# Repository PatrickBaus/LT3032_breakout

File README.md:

LT3032
===================

This repository contains the KiCAD PCB project files for a breakout board for the Linear Technologies LT3032 dual 150 mA,
positive/negative, low noise, LDO (http://www.linear.com/product/LT3032).

About
-----
This breakout board only supports the fixed voltage versions of the LT3032. There are 4 version available:
 * ±3.3V
 * ±5V
 * ±12V
 * ±15V

The root folder contains the KiCAD files and the bill of materials, while the gerber files can be found in the [/gerber](gerber/) folder.

Related Repositories
-------------

See the following repositories for more information

KiCAD footprints: https://github.com/PatrickBaus/footprints.pretty

KiCAD 3D models: https://github.com/PatrickBaus/footprints.3dshapes

KiCAD schematic libraries: https://github.com/PatrickBaus/KiCad-libraries

License
-------

This work is released under the Cern OHL v.1.2
See www.ohwr.org/licenses/cern-ohl/v1.2 or the included LICENSE file for more information.

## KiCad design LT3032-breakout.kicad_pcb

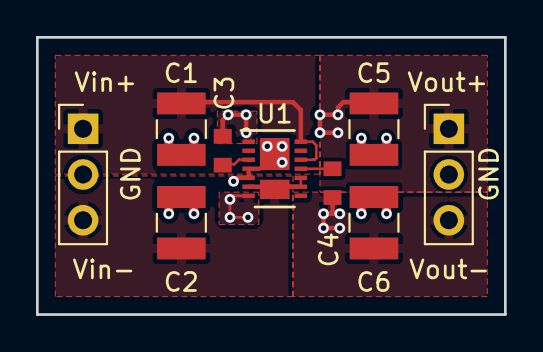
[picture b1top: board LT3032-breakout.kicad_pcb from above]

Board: 2 copper layers, 26.0 x 15.4 mm, 9 parts (0 on the bottom side), 7 nets.

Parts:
C1, C2, C5, C6: 10u; C_1210_3225Metric
C3, C4: 10n; C_0603_1608Metric
J1: Input; PinHeader_1x03_P2.54mm_Vertical
J2: Output; PinHeader_1x03_P2.54mm_Vertical
U1: LT3032-X; Linear_DE14MA

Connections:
/INN: C2.1, J1.3, U1.6, U1.9, U1.10, U1.16
/INP: C1.2, J1.1, U1.12, U1.14
GND: C1.1, C2.2, C5.1, C6.2, J1.2, J2.2, U1.4, U1.5, U1.15
unnamed: C3.1, U1.3
unnamed: C3.2, C5.2, J2.1, U1.1
unnamed: C4.1, C6.1, J2.3, U1.7
unnamed: C4.2, U1.11

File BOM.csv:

"Date:","2018-05-22T07:05:02 CEST"
"Tool:","Eeschema (5.0-dev-4069-g322ce84fb)"
"Component Count:","9"
"Ref","Qnty","Value","Cmp name","Footprint","Description","Vendor"
"C1, C2, C5, C6, ","4","10u","GMK325BJ106KN-T","Capacitor_SMD:C_1210_3225Metric","Unpolarized capacitor","Taiyo Yuden"
"C3, C4, ","2","10n","GRM1885C1H103JA01J","Capacitor_SMD:C_0603_1608Metric","Unpolarized capacitor","Murata"
"J1, ","1","Input","4-103741-0","Connector_PinHeader_2.54mm:PinHeader_1x03_P2.54mm_Vertical","Generic connector, single row, 01x03, script generated (kicad-library-utils/schlib/autogen/connector/)","TE Connectivity"
"J2, ","1","Output","4-103741-0","Connector_PinHeader_2.54mm:PinHeader_1x03_P2.54mm_Vertical","Generic connector, single row, 01x03, script generated (kicad-library-utils/schlib/autogen/connector/)","TE Connectivity"
"U1, ","1","LT3032-X","LT3032-X","Package_DFN_QFN:Linear_DE14MA","Dual 150mA, Positive/Negative Low Noise, Low Dropout Linear Regulator, Fixed Output","Linear Technology"

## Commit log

2017-08-04 Initial release
2017-08-04 Added version number
2017-08-04 Removed unused libraries Added component names
2017-08-04 Added cache file
2017-08-04 Added bill of materials
2017-08-04 Added readme file
2017-08-04 Updated gerber files
2017-08-04 Added render image of the board Updated gitignore file to ignore the XML BOM
2017-08-04 Update README.md
    Fixed link to image
2017-08-04 Update README.md
    Fixed typo
2017-08-24 Added LT3032 footprint
2017-08-25 Added a note to make it more clear that only fixed voltage regulators are supported
2017-10-01 Updated libraries
2017-11-09 Updated libraries Added schematic as PDF
2018-05-22 Updated schematic to KiCAD v5.0
